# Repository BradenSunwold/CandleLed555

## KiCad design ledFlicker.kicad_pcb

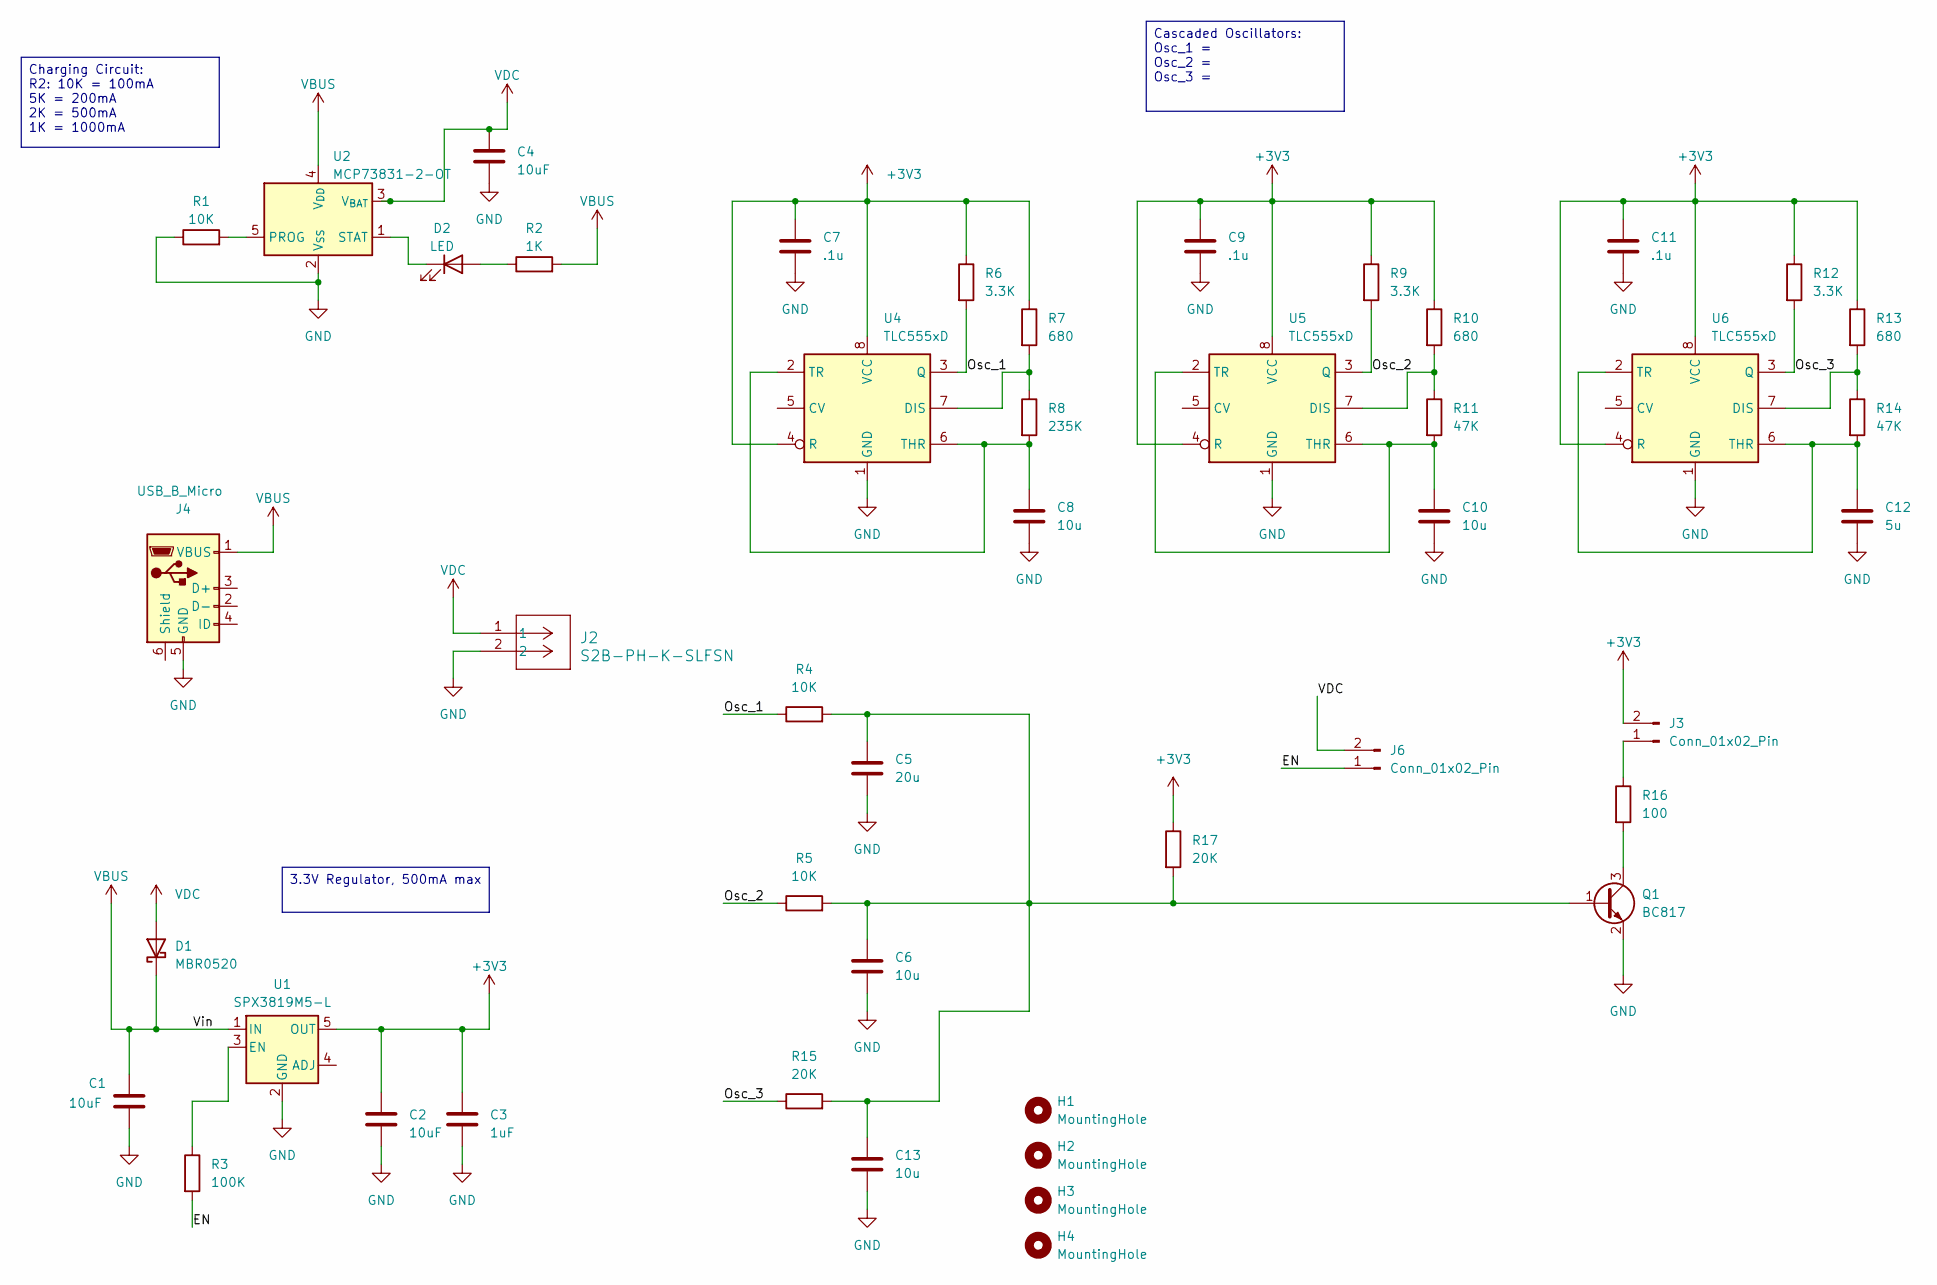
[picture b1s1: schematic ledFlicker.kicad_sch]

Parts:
C1, C2, C4: 10uF; C_0603_1608Metric_Pad1.08x0.95mm_HandSolder
C3: 1uF; C_0603_1608Metric_Pad1.08x0.95mm_HandSolder
C5: 20u; C_0603_1608Metric_Pad1.08x0.95mm_HandSolder
C6, C8, C10, C13: 10u; C_0603_1608Metric_Pad1.08x0.95mm_HandSolder
C7, C9, C11: .1u; C_0603_1608Metric_Pad1.08x0.95mm_HandSolder
C12: 5u; C_0603_1608Metric_Pad1.08x0.95mm_HandSolder
D1: MBR0520; D_SOD-123
D2: LED; LED_0805_2012Metric_Pad1.15x1.40mm_HandSolder
H1, H2, H3, H4: MountingHole; MountingHole_2.2mm_M2
J2: S2B-PH-K-SLFSN; JST_PH_S2B-PH-SM4-TB_1x02-1MP_P2.00mm_Horizontal
J3, J6: Conn_01x02_Pin; PinHeader_1x02_P2.54mm_Vertical
J4: USB_B_Micro; MOLEX_47589-0001
Q1: BC817; SOT-23
R1, R4, R5: 10K; R_0603_1608Metric_Pad0.98x0.95mm_HandSolder
R2: 1K; R_0603_1608Metric_Pad0.98x0.95mm_HandSolder
R3: 100K; R_0603_1608Metric_Pad0.98x0.95mm_HandSolder
R6, R9, R12: 3.3K; R_0603_1608Metric_Pad0.98x0.95mm_HandSolder
R7, R10, R13: 680; R_0603_1608Metric_Pad0.98x0.95mm_HandSolder
R8: 235K; R_0603_1608Metric_Pad0.98x0.95mm_HandSolder
R11, R14: 47K; R_0603_1608Metric_Pad0.98x0.95mm_HandSolder
R15, R17: 20K; R_0603_1608Metric_Pad0.98x0.95mm_HandSolder
R16: 100; R_0603_1608Metric_Pad0.98x0.95mm_HandSolder
U1: SPX3819M5-L; SOT-23-5
U2: MCP73831-2-OT; SOT-23-5
U4, U5, U6: TLC555xD; SOIC-8_3.9x4.9mm_P1.27mm

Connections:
+3V3: C2.1, C3.1, C7.1, C9.1, C11.1, J3.2, R6.1, R7.1, R9.1, R10.1, R12.1, R13.1, R17.1, U1.5 (OUT), U4.4 (R), U4.8 (VCC), U5.4 (R), U5.8 (VCC), U6.4 (R), U6.8 (VCC)
/EN: J6.1, R3.2
/Osc_1: R4.1, R6.2, U4.3 (Q)
/Osc_2: R5.1, R9.2, U5.3 (Q)
/Osc_3: R12.2, R15.1, U6.3 (Q)
GND: C1.2, C2.2, C3.2, C4.2, C5.2, C6.2, C7.2, C8.2, C9.2, C10.2, C11.2, C12.2, C13.2, J2.2, J4.5 (GND), Q1.2 (E), R1.1, U1.2 (GND), U2.2 (V_{SS}), U4.1 (GND), U5.1 (GND), U6.1 (GND)
unnamed: D2.2 (A), R2.1
unnamed: D2.1 (K), U2.1 (STAT)
unnamed: J3.1, R16.1
unnamed: C5.1, C6.1, C13.1, Q1.1 (B), R4.2, R5.2, R15.2, R17.2
unnamed: Q1.3 (C), R16.2
unnamed: R3.1, U1.3 (EN)
unnamed: R1.2, U2.5 (PROG)
unnamed: R7.2, R8.1, U4.7 (DIS)
unnamed: C8.1, R8.2, U4.2 (TR), U4.6 (THR)
unnamed: R10.2, R11.1, U5.7 (DIS)
unnamed: C10.1, R11.2, U5.2 (TR), U5.6 (THR)
unnamed: R13.2, R14.1, U6.7 (DIS)
unnamed: C12.1, R14.2, U6.2 (TR), U6.6 (THR)
VBUS: C1.1, D1.1 (K), J4.1 (VBUS), R2.2, U1.1 (IN), U2.4 (V_{DD})
VDC: C4.1, D1.2 (A), J2.1, J6.2, U2.3 (V_{BAT})

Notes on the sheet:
Charging Circuit: R2: 10K = 100mA 5K = 200mA 2K = 500mA 1K = 1000mA
Cascaded Oscillators: Osc_1 = Osc_2 = Osc_3 =
3.3V Regulator, 500mA max

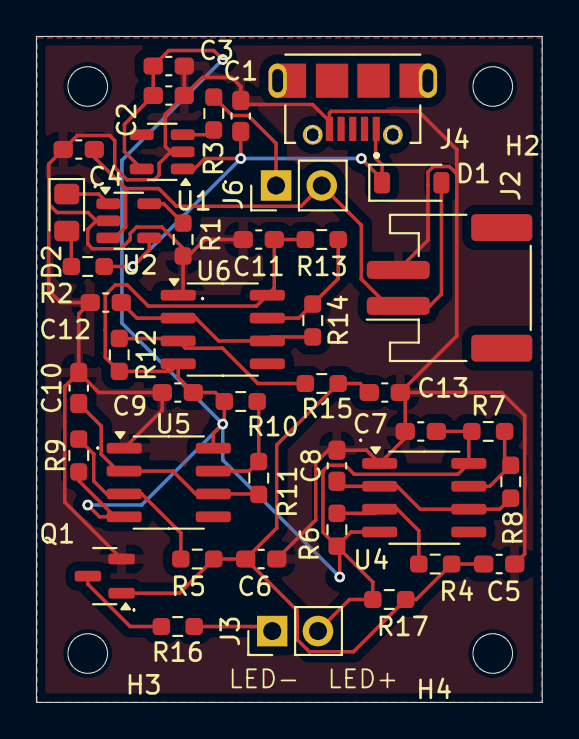
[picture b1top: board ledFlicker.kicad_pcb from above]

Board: 2 copper layers, 28.1 x 37.0 mm, 46 parts (0 on the bottom side), 21 nets.

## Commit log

2025-12-23 Shrunk PCB size, updated switch to OFF, FLICKER only and added R17 bias resistor
2025-12-23 Added enclosure 3D prints to repo
